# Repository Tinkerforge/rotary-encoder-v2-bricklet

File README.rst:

Rotary Encoder Bricklet 2.0
===========================

This repository contains the firmware source code and the hardware design
files. The documentation generator configs can be found at
https://github.com/Tinkerforge/generators

Repository Content
------------------

software/:
 * examples/: Examples for all supported languages
 * build/: Compiled files
 * src/: Source code of firmware
 * Makefile: Makefile to build project

hardware/:
 * Contains KiCad project files and additionally schematics as PDF

datasheets/:
 * Contains datasheets for sensors and complex ICs that are used

Hardware
--------

The hardware is designed with the open source EDA Suite KiCad
(http://www.kicad.org). Before you are able to open the files,
you have to install the Tinkerforge kicad-libraries
(https://github.com/Tinkerforge/kicad-libraries). You can either clone
them directly in hardware/ or clone them in a separate folder and
symlink them into hardware/
(ln -s kicad_path/kicad-libraries project_path/hardware). After that you
can open the .pro file in hardware/ with KiCad and from there view and
modify the schematics and the PCB layout.

Software
--------

If you want to do your own Brick/Bricklet firmware development we highly
recommend that you use our build environment setup script and read the
tutorial (https://www.tinkerforge.com/en/doc/Tutorials/Tutorial_Build_Environment/Tutorial.html).

To compile the C code we recommend you to install the newest GNU Arm Embedded
Toolchain (https://launchpad.net/gcc-arm-embedded/+download).
You also need to install bricklib2 (https://github.com/Tinkerforge/bricklib2).

You can either clone it directly in software/src/ or clone it in a
separate folder and symlink it into software/src/
(ln -s bricklib_path/bricklib2 project_path/software/src/). Finally make sure to
have CMake installed (http://www.cmake.org/cmake/resources/software.html).

After that you can build the firmware by invoking make in software/.
The firmware (.zbin) can then be found in software/build/ and uploaded
with brickv (click button "Flashing" on start screen).

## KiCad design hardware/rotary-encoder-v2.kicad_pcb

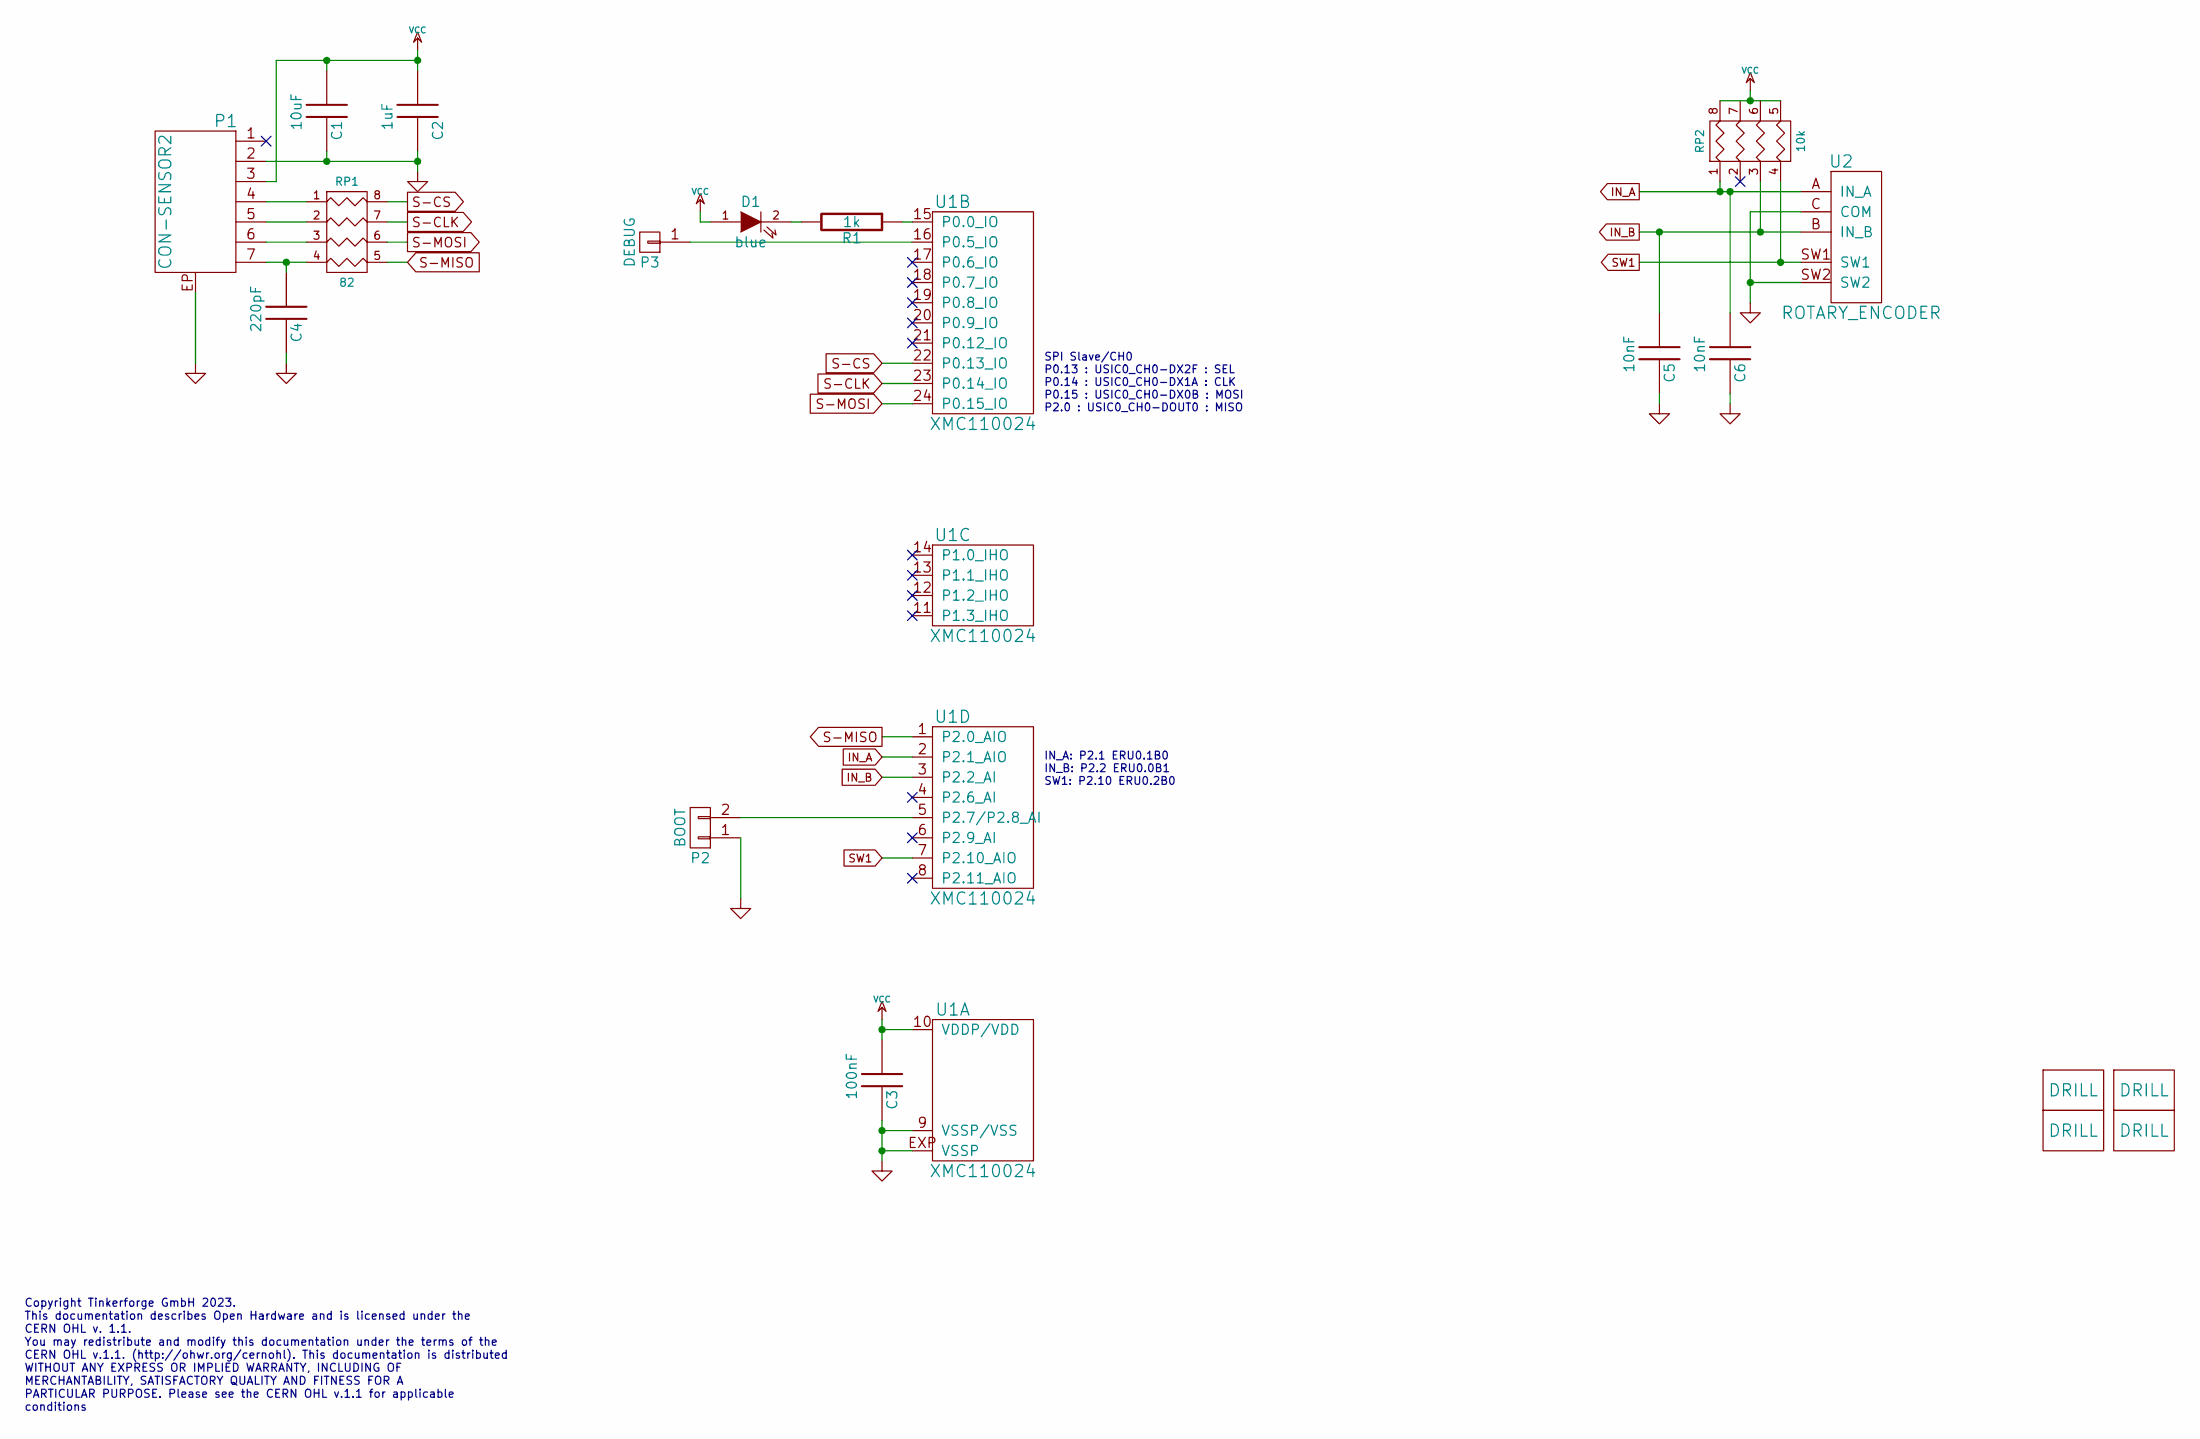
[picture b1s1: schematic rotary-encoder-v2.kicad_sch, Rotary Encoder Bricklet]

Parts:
C1: 10uF; C0805E
C2: 1uF; C0603F
C3: 100nF; C0603F
C4: 220pF; C0402F
C5, C6: 10nF; C0603F
D1: blue; D0603F
P1: CON-SENSOR2
P2: BOOT; SolderJumper
P3: DEBUG; DEBUG_PAD
R1: 1k; R0603F
RP1: 82; 4X0402
RP2: 10k; 4X0603
U1: XMC110024; QFN24-4x4mm-0.5mm
U2: ROTARY_ENCODER
U3, U4, U5, U6: DRILL; DRILL_NP

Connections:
GND: C1.2, C2.2, C3.2, C4.2, C5.2, C6.2, P1.2, P1.EP, P2.1, U1.9 (VSSP/VSS), U1.EXP (VSSP), U2.C (COM), U2.SW2
IN_A: C6.1, RP2.1, U1.2 (P2.1_AIO), U2.A (IN_A)
IN_B: C5.1, RP2.3, U1.3 (P2.2_AI), U2.B (IN_B)
unnamed: C4.1, P1.7, RP1.4
unnamed: D1.2 (K), R1.2
unnamed: P1.4, RP1.1
unnamed: P1.5, RP1.2
unnamed: P1.6, RP1.3
unnamed: P2.2, U1.5 (P2.7/P2.8_AI)
unnamed: P3.1, U1.16 (P0.5_IO)
unnamed: R1.1, U1.15 (P0.0_IO)
S-CLK: RP1.7 (R2), U1.23 (P0.14_IO)
S-CS: RP1.8 (R1), U1.22 (P0.13_IO)
S-MISO: RP1.5 (R4), U1.1 (P2.0_AIO)
S-MOSI: RP1.6 (R3), U1.24 (P0.15_IO)
SW1: RP2.4, U1.7 (P2.10_AIO), U2.SW1
VCC: C1.1, C2.1, C3.1, D1.1 (A), P1.3, RP2.5 (R4), RP2.6 (R3), RP2.7 (R2), RP2.8 (R1), U1.10 (VDDP/VDD)

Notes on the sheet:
IN_A: P2.1 ERU0.1B0 IN_B: P2.2 ERU0.0B1 SW1: P2.10 ERU0.2B0
Copyright Tinkerforge GmbH 2023. This documentation describes Open Hardware and is licensed under the CERN OHL v. 1.1. You may redistribute and modify this documentation under the terms of the CERN OHL v.1.1. (http://ohwr.org/cernohl). This documentation is distributed WITHOUT ANY EXPRESS OR IMPLIE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
SPI Slave/CH0 P0.13 : USIC0_CH0-DX2F : SEL P0.14 : USIC0_CH0-DX1A : CLK P0.15 : USIC0_CH0-DX0B : MOSI P2.0 : USIC0_CH0-DOUT0 : MISO

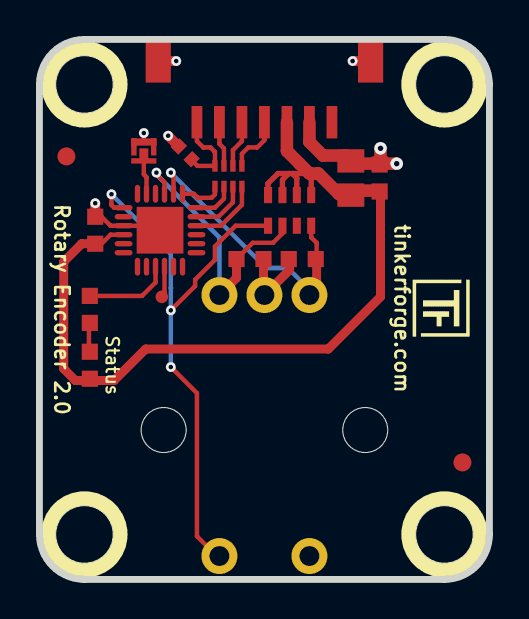
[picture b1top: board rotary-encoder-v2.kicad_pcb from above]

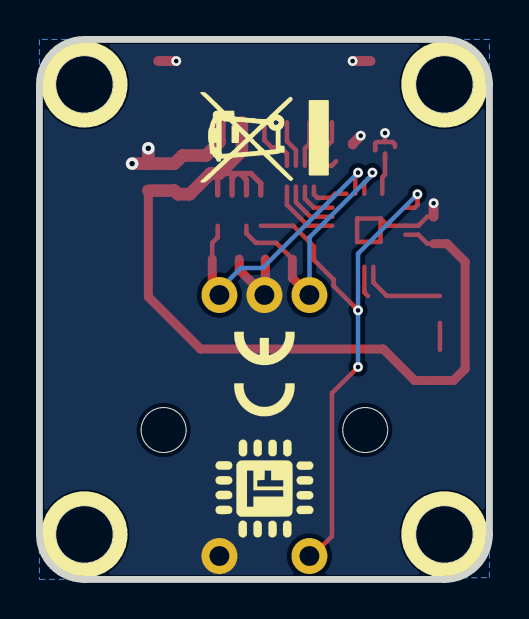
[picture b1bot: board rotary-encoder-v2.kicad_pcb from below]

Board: 2 copper layers, 25.0 x 30.0 mm, 23 parts (2 on the bottom side), 17 nets.

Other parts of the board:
Fiducial_Mark: VAL**; Fiducial_Mark
Fiducial_Mark#2: VAL**; Fiducial_Mark
VAL: WEEE_7mm
VAL#2: CE_5mm

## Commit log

2017-09-15 Add datasheet and license
2017-09-15 Add schematic
2017-09-18 Change pins
2017-09-18 Add PCB
2017-09-18 Finished prototype
2017-09-18 Add logos
2017-10-13 Add initial stub implementation
2017-10-18 change led position
2017-10-25 fix debug pin connection
2017-10-25 add rc capacitors, mode debug
    * add two 10nF capacitors to a,b to remove glitches
    * move debug pin
2017-10-26 Remove obsolete TODOs, disable logging
2017-10-26 Add minimal encoder count implementation
2017-10-26 specify processor type
2018-01-11 Add examples
2018-02-05 Add 3d information (final)
2018-02-05 Add 3d model (*.step & *.FCStd)
2018-02-16 Add schematic (PDF)
2018-02-19 add cutout information
2018-02-19 javascript: Close div tag correctly
2018-02-20 Cleanup KiCad libraries config
    Ensure LibDir=kicad-libraries and LibName1=tinkerforge.
    Remove special library.
2018-02-21 Add count getter/callback implementation
2018-02-21 Use int32_t as callback value type
2018-02-21 Add LabVIEW examples
2018-03-05 Remove unused flash-size define
2018-05-11 Rename files
2018-05-24 perl: Use strict in examples
2018-06-06 Adapt to bricklib2 callback-value changes to fix wrong threshold min/max type
    It was uint16_t but is should have always been int32_t. This changes the
    packet size of the threshold config functions.
2018-06-06 Update changelog and version
2018-06-07 Add date ref for version 2.0.1 to changelog
2018-06-18 Change capacitor footprint(s) to C0402F
2018-06-28 Fix readme
2018-07-11 Add Makefile with docker support
2018-07-11 Remove obsolete generate_makefile scripts
2018-07-11 Update directory structure and build instructions
2018-10-04 Increase version for new release (changes in bricklib2)
2018-10-04 Add rev to changelo
2018-11-06 Add rust examples
2018-11-07 rust: Accept host names for ip connection, fix naming inconsistencies
2018-11-07 rust: Rename callback receivers.
2018-12-14 Add go examples.
2018-12-18 go: Change import path.
2018-12-18 go: Change import path again.
2018-12-20 rust: Reformat examples.
2019-01-18 drc, fix status text
2019-01-24 mqtt: Add examples.
2019-01-24 mqtt: Fix example header.
2019-01-24 mqtt: Remove executable bit in example permissions.
2019-01-24 go: Minor example fixes.
2019-01-24 mqtt: Minor example fixes.
2019-03-25 mqtt: Fix example whitespace.
2019-03-28 mqtt: Fix whitespace.
2019-04-09 Fix bug in reset count logic
2019-04-09 Add ref for 2.0.3
2019-05-29 Disallow SPITFP interrupt to disable IRQs
    The newest version of bricklib2 disables IRQs during SPITFP
    transfers by default. This needs to be turned off for this
    Bricklet since it has higher priority IRQs that can not wait.
    For this we set the SPITFP_NOT_ALLOWED_TO_DISABLE_IRQ define.
2019-05-29 Add rev to changelog
2019-08-22 c: Adapt to bindings changes
2020-01-13 examples: Use python3 input instead of python2 raw_input.
2020-01-13 examples: mqtt: Remove trailing whitespace.
2020-08-19 Add uc examples.
2020-08-25 uc: Fix whitespace
2020-08-27 uc: Fix warnings.
2020-08-31 uc: Use fixed-with placeholders in format strings.
2020-09-02 uc: Add example driver note.
2021-10-25 Update KiCad link
    https://www.kicad.org/blog/2021/10/Avoid-links-to-former-kicad-domain/
2022-04-19 examples: uc: Rename TF_HalContext to TF_HAL.
2022-04-27 uc: Adapt to bindings changes
2022-05-10 go: Fix format string
2022-07-06 Add license files.
2023-01-23 New standart layout. Switched to Kicad 6
2023-01-26 fix symbol libraries
2023-01-26 Data Cleanup
2025-10-04 Fix compatibility with new Docker build image (GCC 14.2.1)

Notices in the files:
hardware/rotary-encoder-v2.kicad_pcb:
Licensed under CERN OHL v.1.1
Copyright (©) 2017, L.Lauer
Copyright Tinkerforge GmbH 2017.
hardware/rotary-encoder-v2.kicad_sch:
Copyright (©) 2023, T.Schneidermann
